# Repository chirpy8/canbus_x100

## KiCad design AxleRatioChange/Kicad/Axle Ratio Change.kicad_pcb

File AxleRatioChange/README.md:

Prototype solution to ‘spoof’ the XKR Mercedes TCM (EGS51 for the W5A580/722.6/NAG1 transmission) in the 4.0 XKR to change the rear axle ratio.
Of course reprogramming the EGS51 TCM would be much better, but there is no readily available developer info I can find to create the appropriate EEPROM profile, and not much interest anymore it seems in this old unit.

This technique might work for other transmissions/TCMs besides the 722.6 (e.g. ZF), or it might not…..

**Disclaimer**

This is not an industrial/automotive grade solution, it is not a commercial or production solution, use at your own risk, not for on-road use, prototype solution for private testing only, no warranty expressed or implied.

**Overview**

The solution is based on an Arduino driven canbus repeater to intercept the messages between the TCM and the rest of the canbus (ECU, ABS, INST).
Two MCP2515 based canbus modules are used, one facing the TCM side of the bus, and the other facing the ECU/ABS side of the bus.
Since the TCM module is conveniently located next to the the ECU in the 2002 XKR, it is easy to snip the canbus wires at the TCM connection, and bridge in the repeater module.
The repeater module receives the messages on the TCM side, and sends them onwards on the ECU/ABS side, and vice versa.
The ABS wheel speed messages towards the TCM are intercepted, and the wheel speed values for all 4 wheels are scaled appropriately so that the TCM is not aware of the different axle ratio, and then sent on.

The code is based on interrupts triggered when a message is received on either canbus. The Arduino communicates with the canbus modules using SPI interface. The interrupt service routines (ISR), one for each direction, read the new message, and then send it back out on the other bus. The ABS facing one also checks for the ABS wheel bus message ID (SID 0x4B0) on ABS side of the bus, and if found it executes the code to scale the speeds. The wheel speeds are big endian 2 byte. Testing to date is limited to a 3.27 axle with 3.06 TCM, but the code includes estimates for the factors for other combinations. The spreadsheet “axle ratio change algorithms” allows computation for factors not listed in the code.

To reduce PCB design efforts, a base PCB design mounts modules that can be purchased on eBay or elsewhere, which saves time and eliminates the need to assemble a board using surface mount components. The compromise is obviously that the solution is bigger.

The design can mount up to 3 canbus modules, the idea being that the third module could be used for off-board telemetry and control. Current testing has only used 2 modules. By not adding the third module, there are convenient connections to add an ICSP connector to program the Arduino, which is used for this specific project.

More details in the docs folder

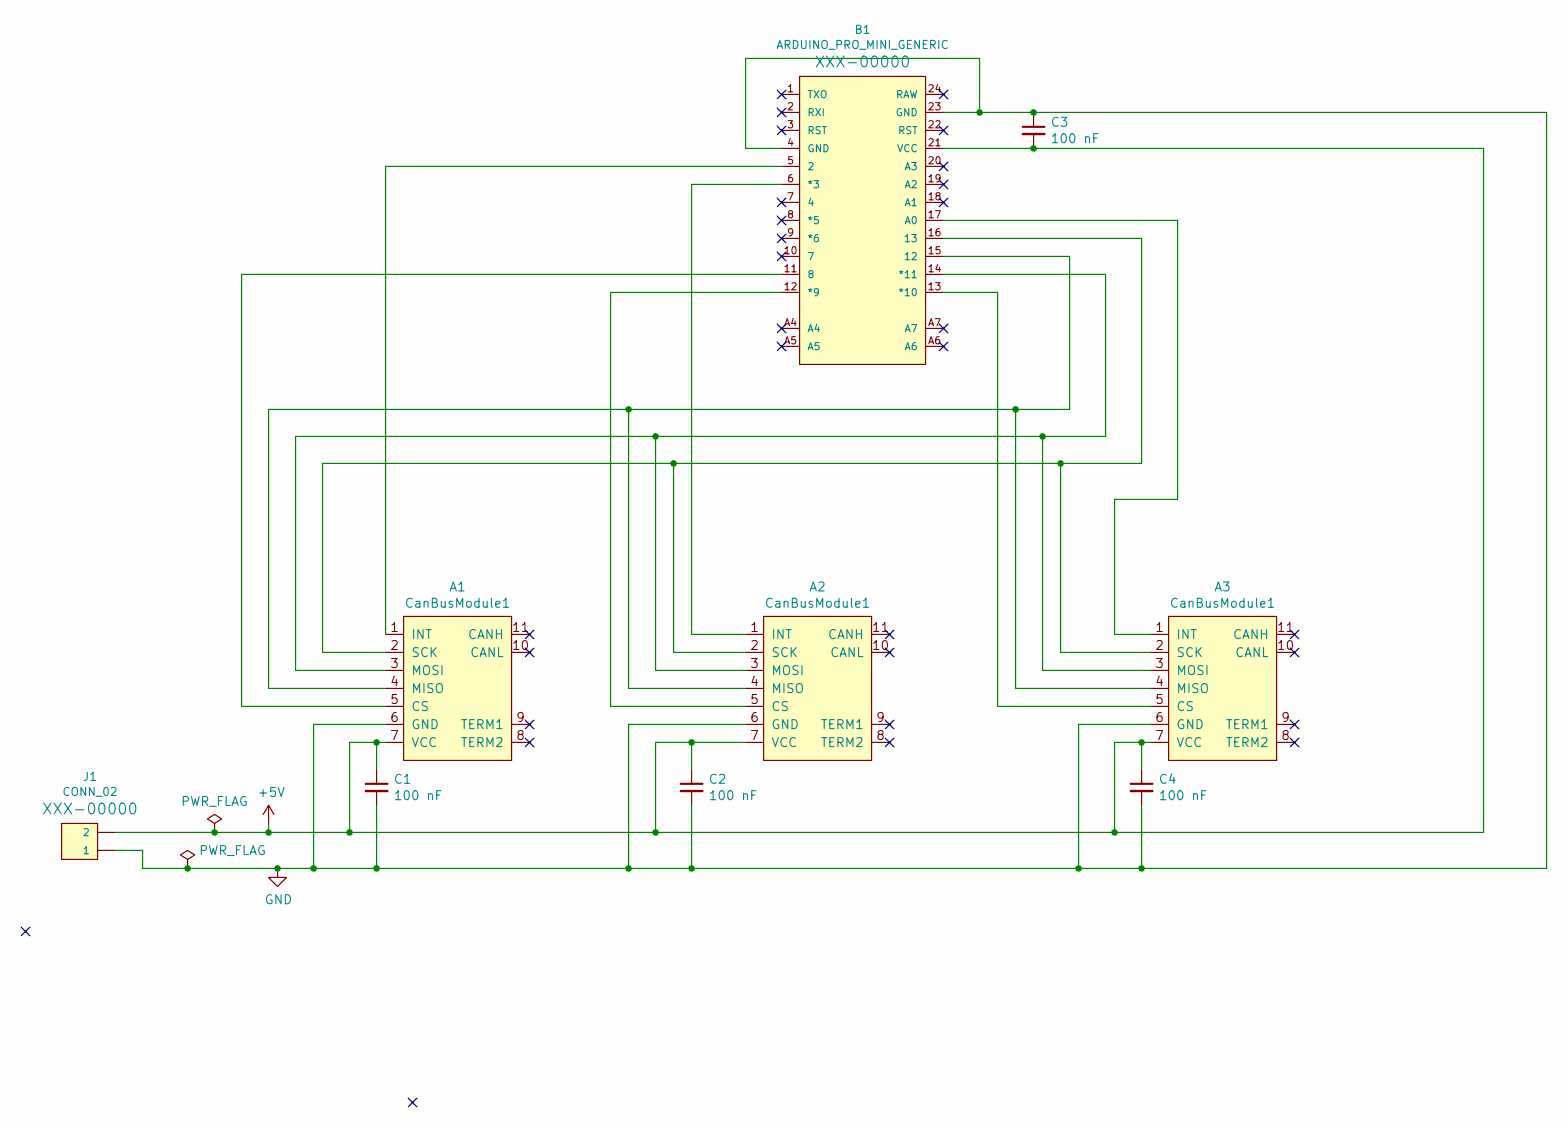
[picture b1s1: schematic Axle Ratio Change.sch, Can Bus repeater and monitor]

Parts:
A1, A2, A3: CanBusModule1
B1: ARDUINO_PRO_MINI_GENERIC; Arduino_Pro_Mini_Generic
C1, C2, C3, C4: 100 nF; C_Disc_D3.0mm_W2.0mm_P2.50mm
J1: CONN_02; 1X02

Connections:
+5V: A1.7 (VCC), A2.7 (VCC), A3.7 (VCC), B1.21 (VCC), C1.1, C2.1, C3.2, C4.1, J1.2
GND: A1.6 (GND), A2.6 (GND), A3.6 (GND), B1.4 (GND), B1.23 (GND), C1.2, C2.2, C3.1, C4.2, J1.1
unnamed: A1.1 (INT), B1.5 (2)
unnamed: A1.2 (SCK), A2.2 (SCK), A3.2 (SCK), B1.16 (13)
unnamed: A1.3 (MOSI), A2.3 (MOSI), A3.3 (MOSI), B1.14 (*11)
unnamed: A1.4 (MISO), A2.4 (MISO), A3.4 (MISO), B1.15 (12)
unnamed: A1.5 (CS), B1.11 (8)
unnamed: A2.1 (INT), B1.6 (*3)
unnamed: A2.5 (CS), B1.12 (*9)
unnamed: A3.1 (INT), B1.17 (A0)
unnamed: A3.5 (CS), B1.13 (*10)

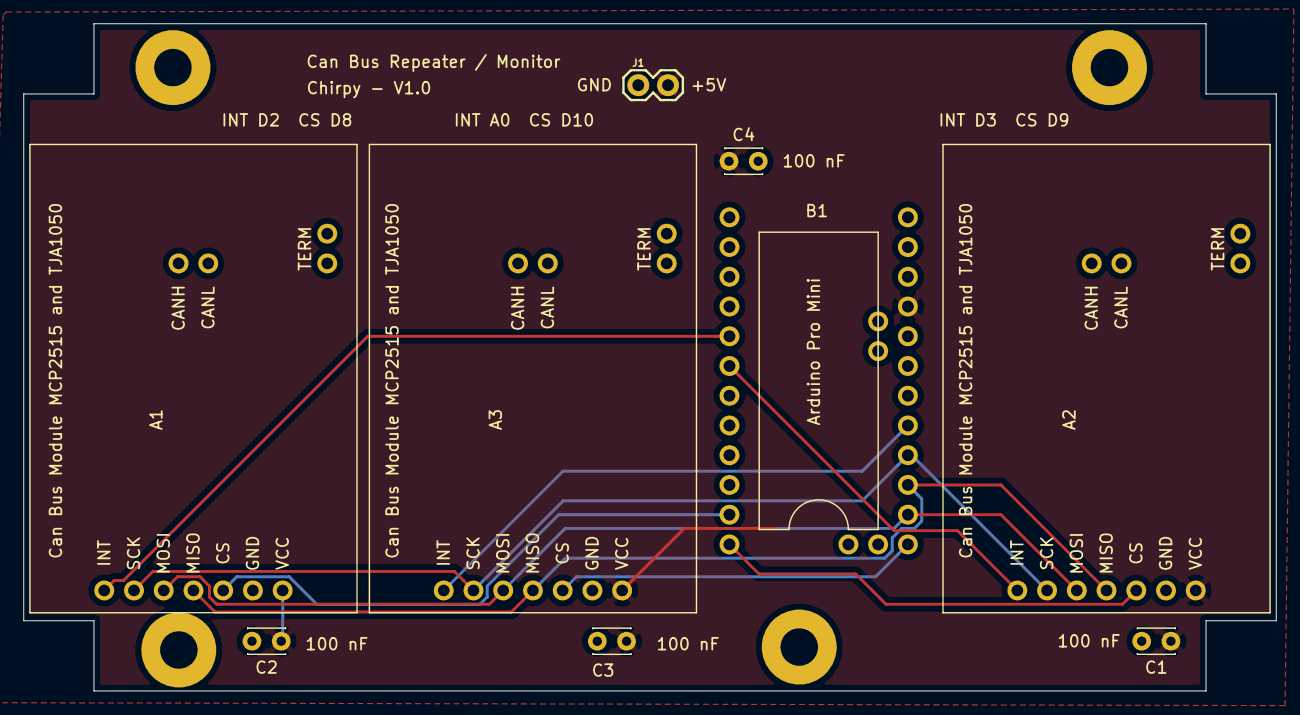
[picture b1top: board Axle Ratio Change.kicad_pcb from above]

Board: 2 copper layers, 107.0 x 57.0 mm, 9 parts (0 on the bottom side), 11 nets.

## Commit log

2021-07-27 initial project version
2021-07-27 Create LICENSE
2025-05-20 Update canbusRatioModifier.ino to address issues with chip reset time variability
    Added significant delay (3.125 us) after each MCP2515 reset command as some board samples seem to require this to function correctly
